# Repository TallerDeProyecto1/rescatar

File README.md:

# rescatAR
El presente proyecto pretende contribuir a disminuir la fatalidad en las rutas argentinas, mediante la integración de la tecnología GSM/GPRS, sensores de aceleración, giroscopios y la Computadora Industrial Abierta Argentina,  en un dispositivo capaz de determinar cuándo se produce un siniestro automovilístico que requiera la intervención de los servicios de asistencia médica y ser capaz de enviar un pedido de socorro.

##Objetivos
El objetivo primario del proyecto consiste en lograr que la CIAA recoja y analice datos de un acelerómetro para detectar colisiones automovilísticas,utilizando un módulo GSM/GPRS para poder reportar las mismas a los servicios de asistencia, contando con un conjunto de teclas y luces para la interacción con el usuario(como por ejemplo un botón de pánico y un botón para cancelar la alerta).
Paralelamente, se desarrolló una aplicación android que instalada en el teléfono que recibe el mensaje SMS de socorro muestra en un mapa interactivo la ubicación del accidente.
Al no poder disponer de un dispositivo GPS, se recurrió a simular  mediante coordenadas arbitrarias la ubicación del pedido de ayuda. No obstante, se pretende seguir avanzando con el proyecto y realizar las modificaciones necesarias para la incorporación de un módulo GPS que permita determinar con precisión la locación del siniestro automovilístico.

## Uso

El proyecto esta dividicdo en distintos modulos organizado en carpetas: 
* [Hardware](https://github.com/TallerDeProyecto1/rescatar/tree/master/Hardware)
* [Software](https://github.com/TallerDeProyecto1/rescatar/tree/master/Software)
* [Aplicacion Android](https://github.com/TallerDeProyecto1/rescatar/tree/master/RescatarApp) 

Cada modulo como se indica a continuacion se desarrolla con diferentes herramientas:

**Hardware**: Abarca los circuitos diseñados para regular la tension de alimentacion de los dispositivos para lo cual utilizo [KiCad](http://kicad-pcb.org/) en su version: (2013-jul-07)-stable

**Software**: El desarrollo del software que corre la edu-ciaa se se realizo utilizando la implementacion de OSEK del _proyecto ciaa_, cabe aclarar que se utilizo la version del firmware que reside en el branch [I2C](https://github.com/ciaa/Firmware/tree/i2c) de repositorio oficial del [proyecto-ciaa](http://www.proyecto-ciaa.com.ar/) debido a la utilizacion de este protocolo. 

**Aplicacion Android**:Se desarrollo con Android Studio version 1.5.0.

## Integrantes del grupo

Minig Traverso Marcelo

Garcia Manuel

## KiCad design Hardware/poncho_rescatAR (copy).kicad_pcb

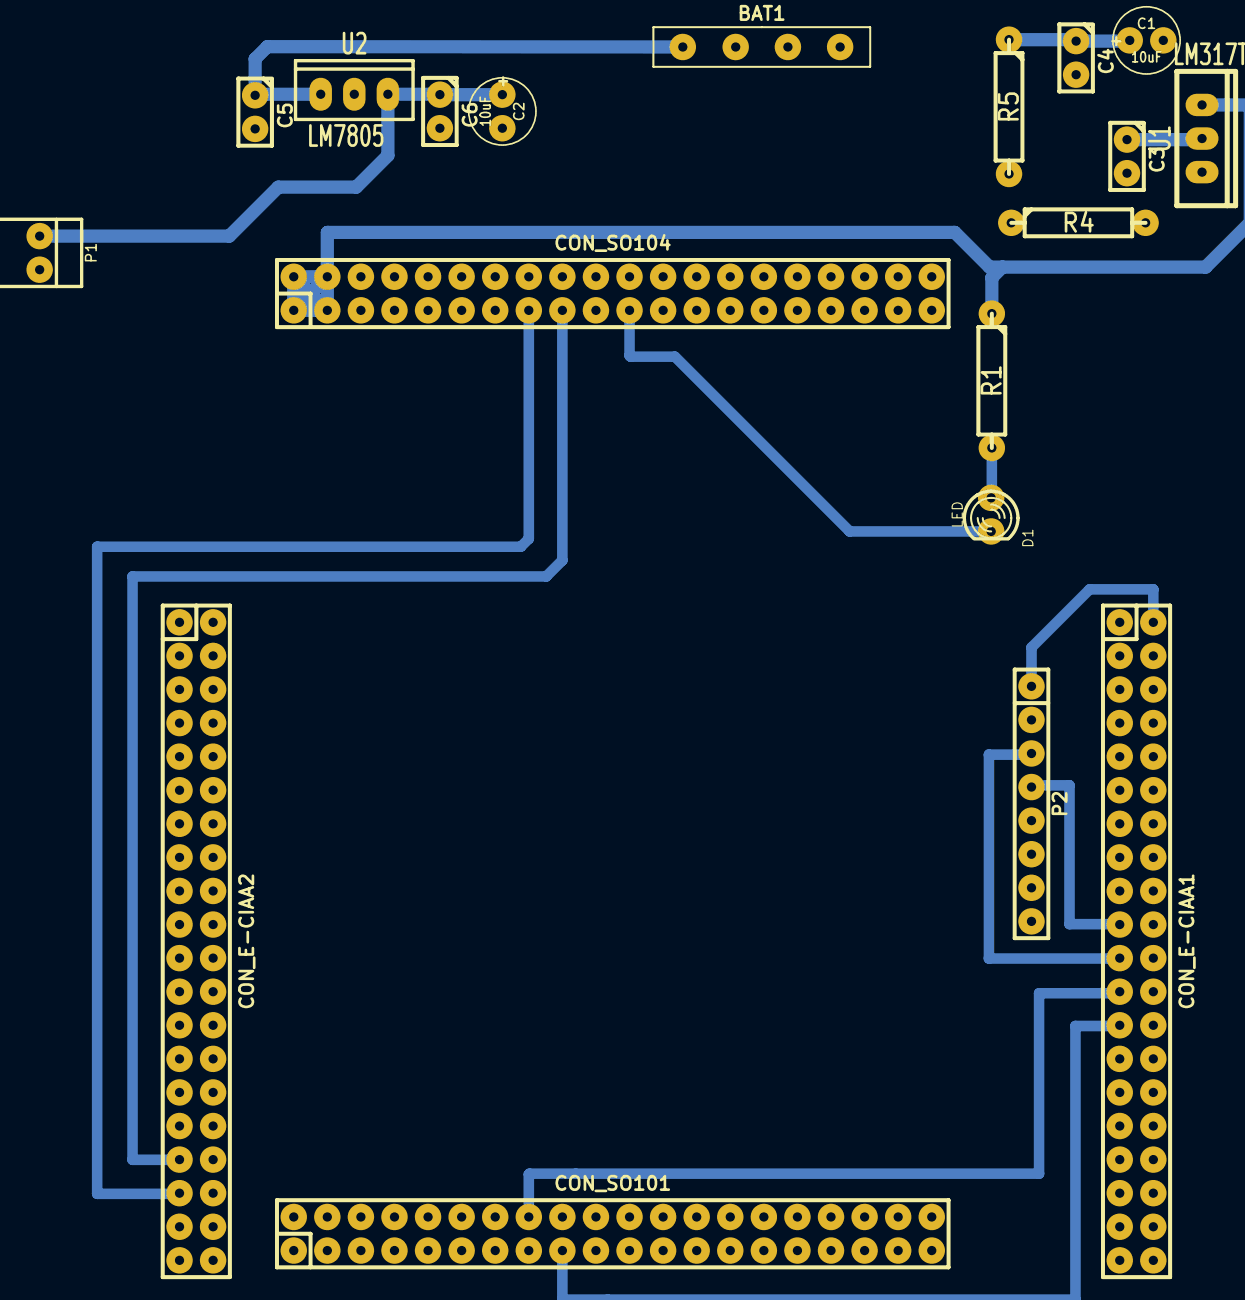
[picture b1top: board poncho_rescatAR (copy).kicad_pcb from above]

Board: 2 copper layers, 19 parts (0 on the bottom side), 15 nets.

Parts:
BAT1: BAT_CONN; PIN_ARRAY_4x1
C1, C2: 10uF; C1V5
C3, C4, C5, C6: 0.1; C1
CON_E-CIAA1, CON_E-CIAA2: CONN_20X2; pin_strip_20x2
CON_SO101, CON_SO104: CONN_20X2; pin_strip_20x2
D1: LED; LED-3MM
P1: 5V_OUT; PINHEAD1-2
P2: CONN_8; pin_strip_8
R1: 330; R4-LARGE_PADS
R4: 470; R4-LARGE_PADS
R5: 220; R4-LARGE_PADS
U1: LM317T; TO220_VERT
U2: LM7805; LM78XXV

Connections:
/GE864_ON_OFF: CON_E-CIAA2.35, CON_SO104.15
/GE864_RESET: CON_E-CIAA2.33, CON_SO104.17
/GND: BAT1.2, C1.2, C2.2, C3.2, C4.2, C5.2, C6.2, CON_E-CIAA1.4, CON_E-CIAA1.20, CON_E-CIAA1.22, CON_E-CIAA1.24, CON_E-CIAA1.26, CON_E-CIAA1.28, CON_E-CIAA1.30, CON_E-CIAA1.32, CON_E-CIAA1.38, CON_E-CIAA1.40, CON_E-CIAA2.3, CON_E-CIAA2.5, CON_E-CIAA2.7, CON_E-CIAA2.11, CON_E-CIAA2.13, CON_E-CIAA2.17, CON_E-CIAA2.19, CON_E-CIAA2.25, CON_E-CIAA2.27, CON_E-CIAA2.37, CON_E-CIAA2.39, CON_SO101.5, CON_SO101.11, CON_SO101.12, CON_SO101.13, CON_SO101.14, CON_SO101.19, CON_SO101.25, CON_SO101.26, CON_SO101.27, CON_SO101.28, CON_SO101.38, CON_SO101.39, CON_SO101.40, CON_SO104.5, CON_SO104.6, CON_SO104.7, CON_SO104.8, CON_SO104.11, CON_SO104.12, CON_SO104.13, CON_SO104.14, CON_SO104.25, CON_SO104.26, CON_SO104.27, CON_SO104.28, CON_SO104.38, CON_SO104.39, CON_SO104.40, P1.2, P2.2, P2.7, R4.2, U2.GND
/I2C_SCL: CON_E-CIAA1.21, P2.3
/I2C_SDA: CON_E-CIAA1.19, P2.4
/RS232_RXD: CON_E-CIAA1.23, CON_SO101.16
/RS232_TXD: CON_E-CIAA1.25, CON_SO101.17
/STATUS_LED: CON_SO104.21, D1.2
/VCC_3.3V: CON_E-CIAA1.1, CON_E-CIAA2.1
/VCC_3.8V: C1.1, C4.1, CON_SO104.1, CON_SO104.2, CON_SO104.3, CON_SO104.4, R1.1, R5.1, U1.2
/VCC_5V: CON_E-CIAA1.2, CON_E-CIAA2.2, P2.1
unnamed: R4.1, R5.2, U1.1
unnamed: C2.1, C6.1, P1.1, U2.VO
unnamed: D1.1, R1.2
VCC: BAT1.1, C3.1, C5.1, U1.3, U2.VI

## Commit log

2015-09-11 add Telit_EVK2_User_Guide_r9
2015-09-17 add schematic gy-521 (breakout board MPU6050)
2015-09-17 Datasheet MPU-6050
2015-09-17 Datasheet MPU-6050 Register Map
2015-09-17 documentacion y datasheets/Datasheet MPU-6050 Register Map
2015-09-20 MPU-6050 header
2015-10-09 Primer commit del esquematico del poncho
2015-10-09 Pequeños arreglos No funcionales al esquematico del poncho
2015-10-09 arreglo error de alimentacion del acelerometro
2015-10-20 Main program and MPU functions
2015-10-29 Arreglos en base a los hablado con el profesor
2015-10-30 Agregue los encabezados de los metodos del modulo GSM
2015-11-04 cambio conector del MPU en el esquematico
2015-11-04 simplificacion del esquematico y comienzo del PCB
2015-11-10 cambios en el esquematico con el regulador de tension para el modulo telit, y el zocalo para la bateria
2015-11-16 check
2015-12-02 retoques finales al esquemetico y pcb base
2015-12-02 perfeccionando el pcb
2015-12-03 mas retoques al pcb, consideracion del boton de reset y los disipadores
2015-12-03 Agregado de capacitores en la alimentacion del acelerometro y pulsador de reset de la ciaa
2015-12-03 que la aplicacion Rescatar sea !
    y la aplicacion fue.
    (para instalarla, pueden poner el app-debug.apk en el telefono pero solo
    puede andar correcto con una version de android mas baja que la 4.3 !)
2015-12-04 retoques al pcb, cambio por el footprint erroneo del LM317
2015-12-04 retoques para prueba final
2015-12-04 rotoques pcb
2015-12-05 Correccion error en PCB y creacion de pdf para tranferir al cobre
2015-12-06 retoques al PCB, agregado de disipadores
2016-01-21 Modificaciones finales al pcb
2016-02-13 Cambio de la clave personal para usar google maps en la app
2016-02-14 SW edu-ciaa final
2016-02-17 ultimos cambios menor en el Software, interfaz luminica y demas
